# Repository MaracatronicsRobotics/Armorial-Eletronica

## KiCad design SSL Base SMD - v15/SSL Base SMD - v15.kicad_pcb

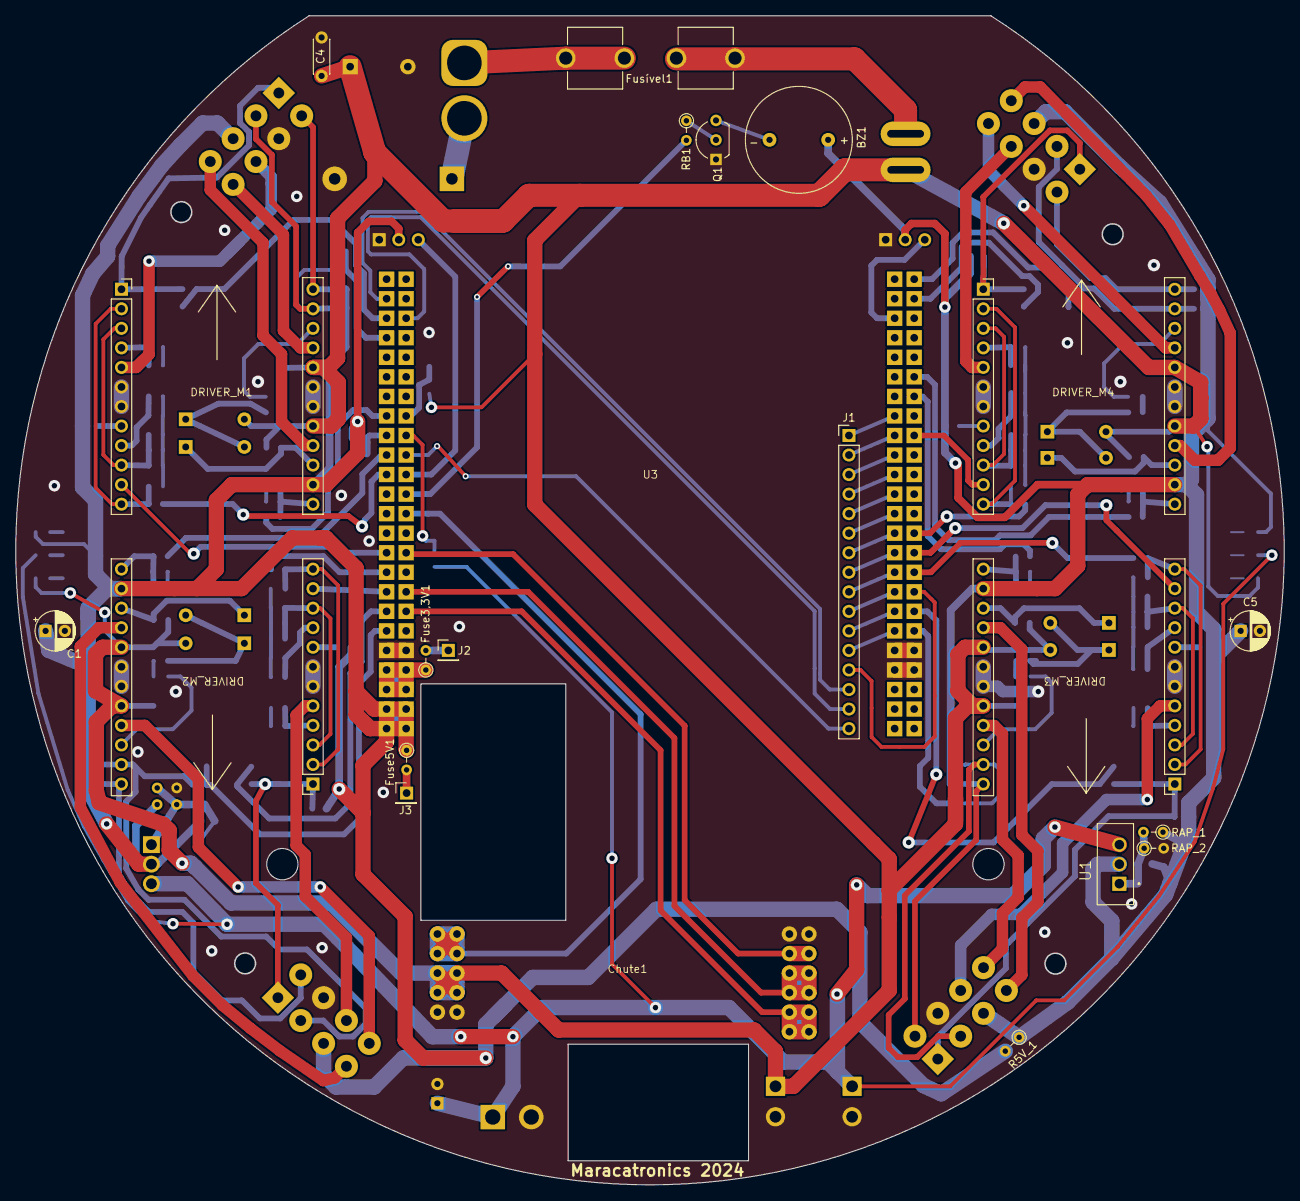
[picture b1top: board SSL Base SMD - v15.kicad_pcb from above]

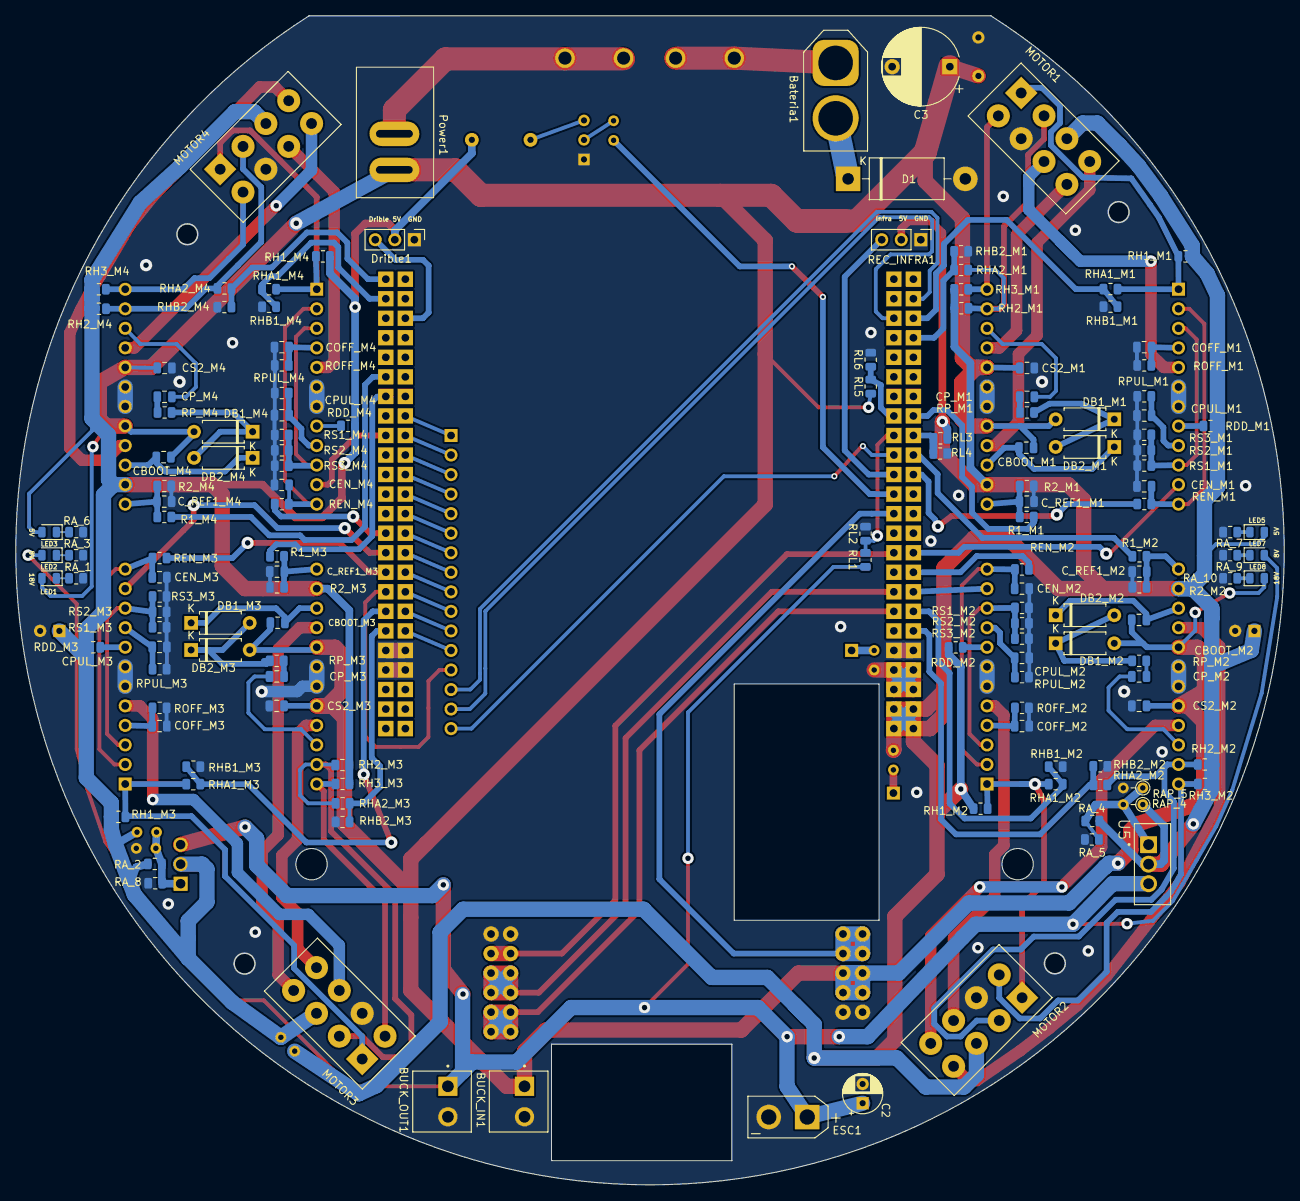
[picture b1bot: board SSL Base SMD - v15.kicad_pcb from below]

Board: 2 copper layers, 164.9 x 152.0 mm, 165 parts (143 on the bottom side), 131 nets.

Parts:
BUCK_IN1: Entrada_Buck_5V; TE_640388-2
BUCK_OUT1: Saida_Buck_5V; TE_640388-2
BZ1: Buzzer; XDCR_CPI-137-12T
Bateria1: Bateria; AMASS_XT60-M_1x02_P7.20mm_Vertical
C1, C2, C5: 100u; CP_Radial_D5.0mm_P2.50mm
C3: 220u; CP_Radial_D10.0mm_P7.50mm
C4: 100n; C_Disc_D4.3mm_W1.9mm_P5.00mm
CBOOT_M1, CBOOT_M2, CBOOT_M3, CBOOT_M4: 220n; C_0805_2012Metric
CEN_M1, CEN_M2, CEN_M3, CEN_M4: 10n; C_0805_2012Metric
COFF_M1, COFF_M2, COFF_M3, COFF_M4: 1n; C_0805_2012Metric
CPUL_M1, CPUL_M2, CPUL_M3, CPUL_M4: 10n; C_0805_2012Metric
CP_M1, CP_M2, CP_M3, CP_M4: 100n; C_0805_2012Metric
CS2_M1, CS2_M2, CS2_M3, CS2_M4: 100n; C_0805_2012Metric
C_REF1_M1, C_REF1_M2, C_REF1_M3, C_REF1_M4: 33n; C_0805_2012Metric
Chute1: Chute1; Conn_2x11x2_Maraca_Chute_Placa
D1: 1N5408; D_DO-201AD_P15.24mm_Horizontal
DB1_M1, DB1_M2, DB1_M3, DB1_M4, DB2_M1, DB2_M2, DB2_M3, DB2_M4: 1N4148; D_A-405_P7.62mm_Horizontal
DRIVER_M1, DRIVER_M2, DRIVER_M3, DRIVER_M4: L6235D; Adaptador L6235
Drible1: JST 3 PIN - ESC; PinHeader_1x03_P2.54mm_Vertical
ESC1: XT30PB - ESC_DRIBLE_POWER; AMASS_XT30UPB-F_1x02_P5.0mm_Vertical
Fuse3,3V1, Fuse5V1: 0; R_Axial_DIN0204_L3.6mm_D1.6mm_P2.54mm_Vertical
Fusível1: Fusível; FUSE_BK-6003M
J1: Conn_01x16; PinHeader_1x16_P2.54mm_Vertical
J2, J3: Conn_01x01; PinHeader_1x01_P2.54mm_Vertical
LED1, LED2, LED3, LED5, LED7, LED8: NCD0805R1; LED_0805_2012Metric
MOTOR1: CONECTOR MOTOR 1; TE_1586037-8b
MOTOR2: CONECTOR MOTOR 2; TE_1586037-8b
MOTOR3: CONECTOR MOTOR 3; TE_1586037-8b
MOTOR4: CONECTOR MOTOR 4; TE_1586037-8b
Power1: INTERRUPTOR; E-SWITCH_Maraca
Q1: 2N3904; TO-92L_Inline_Wide
R1_M1, R1_M2, R1_M3, R1_M4: 22k; R_0805_2012Metric
R2_M1, R2_M2, R2_M3, R2_M4: 3.3k; R_0805_2012Metric
R5V_1: 0; R_Axial_DIN0204_L3.6mm_D1.6mm_P2.54mm_Vertical
RAP_1, RAP_4: 1k; R_Axial_DIN0204_L3.6mm_D1.6mm_P2.54mm_Vertical
RAP_2, RAP_5: 3.3k; R_Axial_DIN0204_L3.6mm_D1.6mm_P2.54mm_Vertical
RA_1, RA_10: 2.2k; R_0805_2012Metric
RA_2, RA_3, RA_4, RA_9: 1k; R_0805_2012Metric
RA_5, RA_8: 3.3k; R_0805_2012Metric
RA_6, RA_7: 470; R_0805_2012Metric
RB1: 220; R_Axial_DIN0204_L3.6mm_D1.6mm_P2.54mm_Vertical
RDD_M1, RDD_M2, RDD_M3, RDD_M4: 1k; R_0805_2012Metric
REC_INFRA1: JST 3 PIN - INFRA; PinHeader_1x03_P2.54mm_Vertical
REN_M1, REN_M2, REN_M3, REN_M4: 100k; R_0805_2012Metric
RH1_M1, RH1_M2, RH1_M3, RH1_M4, RH2_M1, RH2_M2, RH2_M3, RH2_M4, RH3_M1, RH3_M2, RH3_M3, RH3_M4: 10k; R_0805_2012Metric
RHA1_M1, RHA1_M2, RHA1_M3, RHA1_M4, RHA2_M1, RHA2_M2, RHA2_M3, RHA2_M4: 1k; R_0805_2012Metric
RHB1_M1, RHB1_M2, RHB1_M3, RHB1_M4, RHB2_M1, RHB2_M2, RHB2_M3, RHB2_M4: 2.2k; R_0805_2012Metric
RL1, RL3, RL5: 10M; R_0805_2012Metric
RL2, RL4, RL6: 1M; R_0805_2012Metric
ROFF_M1, ROFF_M2, ROFF_M3, ROFF_M4: 33k; R_0805_2012Metric
RPUL_M1, RPUL_M2, RPUL_M3, RPUL_M4: 47k; R_0805_2012Metric
RP_M1, RP_M2, RP_M3, RP_M4: 100; R_0805_2012Metric
RS1_M1, RS1_M2, RS1_M3, RS1_M4, RS2_M1, RS2_M2, RS2_M3, RS2_M4, RS3_M1, RS3_M2, RS3_M3, RS3_M4: 1; R_0805_2012Metric
U1, U5: LM338T; TO254P1054X470X1955-3
U3: STM32F401VETx; STM32MARACA_3D

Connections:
3,3V: Fuse3,3V1.1, U3.69 (+3.3V_(4)), U3.70 (+3.3V_(3)), U3.93 (+3.3V_(2)), U3.94 (+3.3V_(1))
5BV: BZ1.1 (-), C5.1, DRIVER_M3.14 (BRAKE), DRIVER_M4.14 (BRAKE), Drible1.2, LED3.2 (A), MOTOR3.3, MOTOR4.3, R5V_1.1, RAP_1.1, RA_2.1, RDD_M3.1, RDD_M4.1, RH1_M3.2, RH1_M4.2, RH2_M3.2, RH2_M4.2, RH3_M3.2, RH3_M4.2, U1.2 (VOUT)
5V: C1.1, DRIVER_M1.14 (BRAKE), DRIVER_M2.14 (BRAKE), Fuse5V1.1, LED5.2 (A), MOTOR1.3, MOTOR2.3, R5V_1.2, RAP_4.1, RA_4.1, RDD_M1.1, RDD_M2.1, REC_INFRA1.2, RH1_M1.2, RH1_M2.2, RH2_M1.2, RH2_M2.2, RH3_M1.2, RH3_M2.2, RL3.1, U3.71 (+5V_(4)), U3.72 (+5V_(3)), U3.95 (+5V_(2)), U3.96 (+5V_(1)), U5.2 (VOUT)
8V: BUCK_OUT1.1, C2.1, ESC1.1, LED2.2 (A), LED7.2 (A), RL1.1, U1.3 (VIN), U5.3 (VIN)
18V: BUCK_IN1.1, C3.1, C4.1, CBOOT_M1.1, CBOOT_M2.1, CBOOT_M3.1, CBOOT_M4.1, CS2_M1.1, CS2_M2.1, CS2_M3.1, CS2_M4.1, Chute1.3, Chute1.4, DB1_M1.2 (A), DB1_M2.2 (A), DB1_M3.2 (A), DB1_M4.2 (A), DRIVER_M1.17 (VSB), DRIVER_M1.20 (VSA), DRIVER_M2.17 (VSB), DRIVER_M2.20 (VSA), DRIVER_M3.17 (VSB), DRIVER_M3.20 (VSA), DRIVER_M4.17 (VSB), DRIVER_M4.20 (VSA), LED1.2 (A), LED8.2 (A), Power1.1, RL5.1
ADC_Chute: Chute1.7, U3.63 (PC_3)
AnalogIN: J1.16, U3.58 (PA_7)
BAT_NEG: Bateria1.2, D1.1 (K)
BAT_POS: Bateria1.1, Fusível1.2
Buzzer: RB1.2, U3.60 (PA_3)
DIAG/EN_M1: CEN_M1.1, DRIVER_M1.2 (DIAG), DRIVER_M1.12 (EN), REN_M1.2
DIAG/EN_M2: CEN_M2.1, DRIVER_M2.2 (DIAG), DRIVER_M2.12 (EN), REN_M2.2
DIAG/EN_M3: CEN_M3.1, DRIVER_M3.2 (DIAG), DRIVER_M3.12 (EN), REN_M3.2
DIAG/EN_M4: CEN_M4.1, DRIVER_M4.2 (DIAG), DRIVER_M4.12 (EN), REN_M4.2
DISPARO CHIP KICK: Chute1.10, Chute1.11, U3.66 (PE_5)
DISPARO NORMAL: Chute1.8, Chute1.9, U3.65 (PC_13)
DRIBLE: Drible1.3, U3.27 (PD_12)
EN_M1: REN_M1.1, U3.83 (PA_4)
EN_M2: REN_M2.1, U3.88 (PC_0)
EN_M3: REN_M3.1, U3.16 (PB_3)
EN_M4: REN_M4.1, U3.14 (PD_4)
FWD/REV_M1: DRIVER_M1.11 (FWD/REV), U3.87 (PC_2)
FWD/REV_M2: DRIVER_M2.11 (FWD/REV), U3.89 (PE_6)
FWD/REV_M3: DRIVER_M3.11 (FWD/REV), U3.15 (PD_6)
FWD/REV_M4: DRIVER_M4.11 (FWD/REV), U3.9 (PA_11)
GND: BUCK_IN1.2, BUCK_OUT1.2, C1.2, C2.2, C3.2, C4.2, C5.2, CEN_M1.2, CEN_M2.2, CEN_M3.2, CEN_M4.2, COFF_M1.2, COFF_M2.2, COFF_M3.2, COFF_M4.2, CPUL_M1.2, CPUL_M2.2, CPUL_M3.2, CPUL_M4.2, CS2_M1.2, CS2_M2.2, CS2_M3.2, CS2_M4.2, C_REF1_M1.2, C_REF1_M2.2, C_REF1_M3.2, C_REF1_M4.2, Chute1.5, Chute1.6, D1.2 (A), DRIVER_M1.6 (GND), DRIVER_M1.7 (GND), DRIVER_M1.18 (GND), DRIVER_M1.19 (GND), DRIVER_M2.6 (GND), DRIVER_M2.7 (GND), DRIVER_M2.18 (GND), DRIVER_M2.19 (GND), DRIVER_M3.6 (GND), DRIVER_M3.7 (GND), DRIVER_M3.18 (GND), DRIVER_M3.19 (GND), DRIVER_M4.6 (GND), DRIVER_M4.7 (GND), DRIVER_M4.18 (GND), DRIVER_M4.19 (GND), Drible1.1, ESC1.2, MOTOR1.6, MOTOR2.6, MOTOR3.6, MOTOR4.6, Q1.1 (E), R2_M1.2, R2_M2.2, R2_M3.2, R2_M4.2, RAP_2.2, RAP_5.2, RA_1.2, RA_3.2, RA_5.2, RA_6.2, RA_7.2, RA_8.2, RA_9.2, RA_10.2, REC_INFRA1.1, RHB1_M1.2, RHB1_M2.2, RHB1_M3.2, RHB1_M4.2, RHB2_M1.2, RHB2_M2.2, RHB2_M3.2, RHB2_M4.2, RL2.2, RL4.2, RL6.2, ROFF_M1.2, ROFF_M2.2, ROFF_M3.2, ROFF_M4.2, RPUL_M1.2, RPUL_M2.2, RPUL_M3.2, RPUL_M4.2, RS1_M1.1, RS1_M2.1, RS1_M3.1, RS1_M4.1, RS2_M1.1, RS2_M2.1, RS2_M3.1, RS2_M4.1, RS3_M1.1, RS3_M2.1, RS3_M3.1, RS3_M4.1, U3.20 (GND_(6)), U3.21 (GND_(5)), U3.44 (GND_(4)), U3.45 (GND_(3)), U3.68 (GND_(2)), U3.92 (GND_(1))
H1_M1: RHA1_M1.2, RHB1_M1.1, U3.75 (PE_15)
H1_M2: RHA1_M2.2, RHB1_M2.1, U3.90 (PE_4)
H1_M3: RHA1_M3.2, RHB1_M3.1, U3.18 (PB_8)
H1_M4: RHA1_M4.2, RHB1_M4.1, U3.2 (PD_9)
H2_M1: RHA2_M1.2, RHB2_M1.1, U3.76 (PE_13)
H2_M2: RHA2_M2.2, RHB2_M2.1, U3.91 (PE_2)
H2_M3: RHA2_M3.2, RHB2_M3.1, U3.19 (PE_0)
H2_M4: RHA2_M4.2, RHB2_M4.1, U3.1 (PB_15)
HALL1_M1: DRIVER_M1.1 (H1), MOTOR1.1, RH1_M1.1, RHA1_M1.1
HALL1_M2: DRIVER_M2.1 (H1), MOTOR2.1, RH1_M2.1, RHA1_M2.1
HALL1_M3: DRIVER_M3.1 (H1), MOTOR3.1, RH1_M3.1, RHA1_M3.1
HALL1_M4: DRIVER_M4.1 (H1), MOTOR4.1, RH1_M4.1, RHA1_M4.1
HALL2_M1: DRIVER_M1.23 (H2), MOTOR1.2, RH2_M1.1, RHA2_M1.1
HALL2_M2: DRIVER_M2.23 (H2), MOTOR2.2, RH2_M2.1, RHA2_M2.1
HALL2_M3: DRIVER_M3.23 (H2), MOTOR3.2, RH2_M3.1, RHA2_M3.1
HALL2_M4: DRIVER_M4.23 (H2), MOTOR4.2, RH2_M4.1, RHA2_M4.1
HALL3_M1: DRIVER_M1.24 (H3), MOTOR1.5, RH3_M1.1
HALL3_M2: DRIVER_M2.24 (H3), MOTOR2.5, RH3_M2.1
HALL3_M3: DRIVER_M3.24 (H3), MOTOR3.5, RH3_M3.1
HALL3_M4: DRIVER_M4.24 (H3), MOTOR4.5, RH3_M4.1
INFRA: REC_INFRA1.3, U3.59 (PA_5)
LEITURA_5V: RL3.2, RL4.1, U3.81 (PC_4)
LEITURA_8V: RL1.2, RL2.1, U3.57 (PC_5)
LEITURA_BATERIA: RL5.2, RL6.1, U3.56 (PB_1)
MOTOR1_1: DRIVER_M1.5 (OUT1), MOTOR1.7
MOTOR1_2: DRIVER_M1.21 (OUT2), MOTOR1.8
MOTOR1_3: DRIVER_M1.16 (OUT3), MOTOR1.4
MOTOR2_1: DRIVER_M2.5 (OUT1), MOTOR2.7
MOTOR2_2: DRIVER_M2.21 (OUT2), MOTOR2.8
MOTOR2_3: DRIVER_M2.16 (OUT3), MOTOR2.4
MOTOR3_1: DRIVER_M3.5 (OUT1), MOTOR3.7
MOTOR3_2: DRIVER_M3.21 (OUT2), MOTOR3.8
MOTOR3_3: DRIVER_M3.16 (OUT3), MOTOR3.4
MOTOR4_1: DRIVER_M4.5 (OUT1), MOTOR4.7
MOTOR4_2: DRIVER_M4.21 (OUT2), MOTOR4.8
MOTOR4_3: DRIVER_M4.16 (OUT3), MOTOR4.4
unnamed: BZ1.2 (+), Q1.3 (C)
unnamed: CP_M1.2, RP_M1.1
unnamed: CP_M2.2, RP_M2.1
unnamed: CP_M3.2, RP_M3.1
unnamed: CP_M4.2, RP_M4.1
unnamed: DB1_M1.1 (K), DB2_M1.2 (A), RP_M1.2
unnamed: DB1_M2.1 (K), DB2_M2.2 (A), RP_M2.2
unnamed: DB1_M3.1 (K), DB2_M3.2 (A), RP_M3.2
unnamed: DB1_M4.1 (K), DB2_M4.2 (A), RP_M4.2
unnamed: Fusível1.1, Power1.2
unnamed: LED1.1 (K), RA_1.1
unnamed: LED2.1 (K), RA_3.1
unnamed: LED3.1 (K), RA_6.1
unnamed: LED5.1 (K), RA_7.1
unnamed: LED7.1 (K), RA_9.1
unnamed: LED8.1 (K), RA_10.1
unnamed: Q1.2 (B), RB1.1
unnamed: RAP_1.2, RAP_2.1, RA_2.2, RA_8.1, U1.1 (ADJ)
unnamed: RAP_4.2, RAP_5.1, RA_4.2, RA_5.1, U5.1 (ADJ)
Out 3,3V: Fuse3,3V1.2, J2.1
Out 5V: Fuse5V1.2, J3.1
PA10: J1.1, U3.32 (PA_10)
PA12: J1.2, U3.33 (PA_12)
PB5: J1.9, U3.40 (PB_5)
PB6: J1.13, U3.17 (PB_6)
PB7: J1.10, U3.41 (PB_7)
PB9: J1.11, U3.42 (PB_9)
PB10: J1.15, U3.51 (PB_10)
PB11: J1.14, U3.74 (PB_11)
PC10: J1.3, U3.34 (PC_10)
PC12: J1.4, U3.35 (PC_12)
PD1: J1.5, U3.36 (PD_1)
PD3: J1.6, U3.37 (PD_3)
PD5: J1.7, U3.38 (PD_5)
PD7: J1.8, U3.39 (PD_7)
PE1: J1.12, U3.43 (PE_1)
PWM_Carregamento: Chute1.1, Chute1.2, U3.61 (PA_1)
PWM_RODA_1: R1_M1.2, U3.80 (PB_0)
PWM_RODA_2: R1_M2.2, U3.82 (PA_6)
PWM_RODA_3: R1_M3.2, U3.7 (PC_9)
PWM_RODA_4: R1_M4.2, U3.6 (PC_7)
RCOFF_M1: COFF_M1.1, DRIVER_M1.4 (RCOFF), ROFF_M1.1
RCOFF_M2: COFF_M2.1, DRIVER_M2.4 (RCOFF), ROFF_M2.1
RCOFF_M3: COFF_M3.1, DRIVER_M3.4 (RCOFF), ROFF_M3.1
RCOFF_M4: COFF_M4.1, DRIVER_M4.4 (RCOFF), ROFF_M4.1
RCPULSE_M1: CPUL_M1.1, DRIVER_M1.9 (RCPULSE), RPUL_M1.1
RCPULSE_M2: CPUL_M2.1, DRIVER_M2.9 (RCPULSE), RPUL_M2.1
RCPULSE_M3: CPUL_M3.1, DRIVER_M3.9 (RCPULSE), RPUL_M3.1
RCPULSE_M4: CPUL_M4.1, DRIVER_M4.9 (RCPULSE), RPUL_M4.1
SENSE_M1: DRIVER_M1.3 (SENSEA), DRIVER_M1.10 (SENSEB), RS1_M1.2, RS2_M1.2, RS3_M1.2
SENSE_M2: DRIVER_M2.3 (SENSEA), DRIVER_M2.10 (SENSEB), RS1_M2.2, RS2_M2.2, RS3_M2.2
SENSE_M3: DRIVER_M3.3 (SENSEA), DRIVER_M3.10 (SENSEB), RS1_M3.2, RS2_M3.2, RS3_M3.2
SENSE_M4: DRIVER_M4.3 (SENSEA), DRIVER_M4.10 (SENSEB), RS1_M4.2, RS2_M4.2, RS3_M4.2
TACHO_M1: DRIVER_M1.8 (TACHO), RDD_M1.2
TACHO_M2: DRIVER_M2.8 (TACHO), RDD_M2.2
TACHO_M3: DRIVER_M3.8 (TACHO), RDD_M3.2
TACHO_M4: DRIVER_M4.8 (TACHO), RDD_M4.2
VBOOT_M1: CBOOT_M1.2, DB2_M1.1 (K), DRIVER_M1.15 (VBOOT)
VBOOT_M2: CBOOT_M2.2, DB2_M2.1 (K), DRIVER_M2.15 (VBOOT)
VBOOT_M3: CBOOT_M3.2, DB2_M3.1 (K), DRIVER_M3.15 (VBOOT)
VBOOT_M4: CBOOT_M4.2, DB2_M4.1 (K), DRIVER_M4.15 (VBOOT)
VCP_M1: CP_M1.1, DRIVER_M1.22 (VCP)
VCP_M2: CP_M2.1, DRIVER_M2.22 (VCP)
VCP_M3: CP_M3.1, DRIVER_M3.22 (VCP)
VCP_M4: CP_M4.1, DRIVER_M4.22 (VCP)
VREF_M1: C_REF1_M1.1, DRIVER_M1.13 (VREF), R1_M1.1, R2_M1.1
VREF_M2: C_REF1_M2.1, DRIVER_M2.13 (VREF), R1_M2.1, R2_M2.1
VREF_M3: C_REF1_M3.1, DRIVER_M3.13 (VREF), R1_M3.1, R2_M3.1
VREF_M4: C_REF1_M4.1, DRIVER_M4.13 (VREF), R1_M4.1, R2_M4.1

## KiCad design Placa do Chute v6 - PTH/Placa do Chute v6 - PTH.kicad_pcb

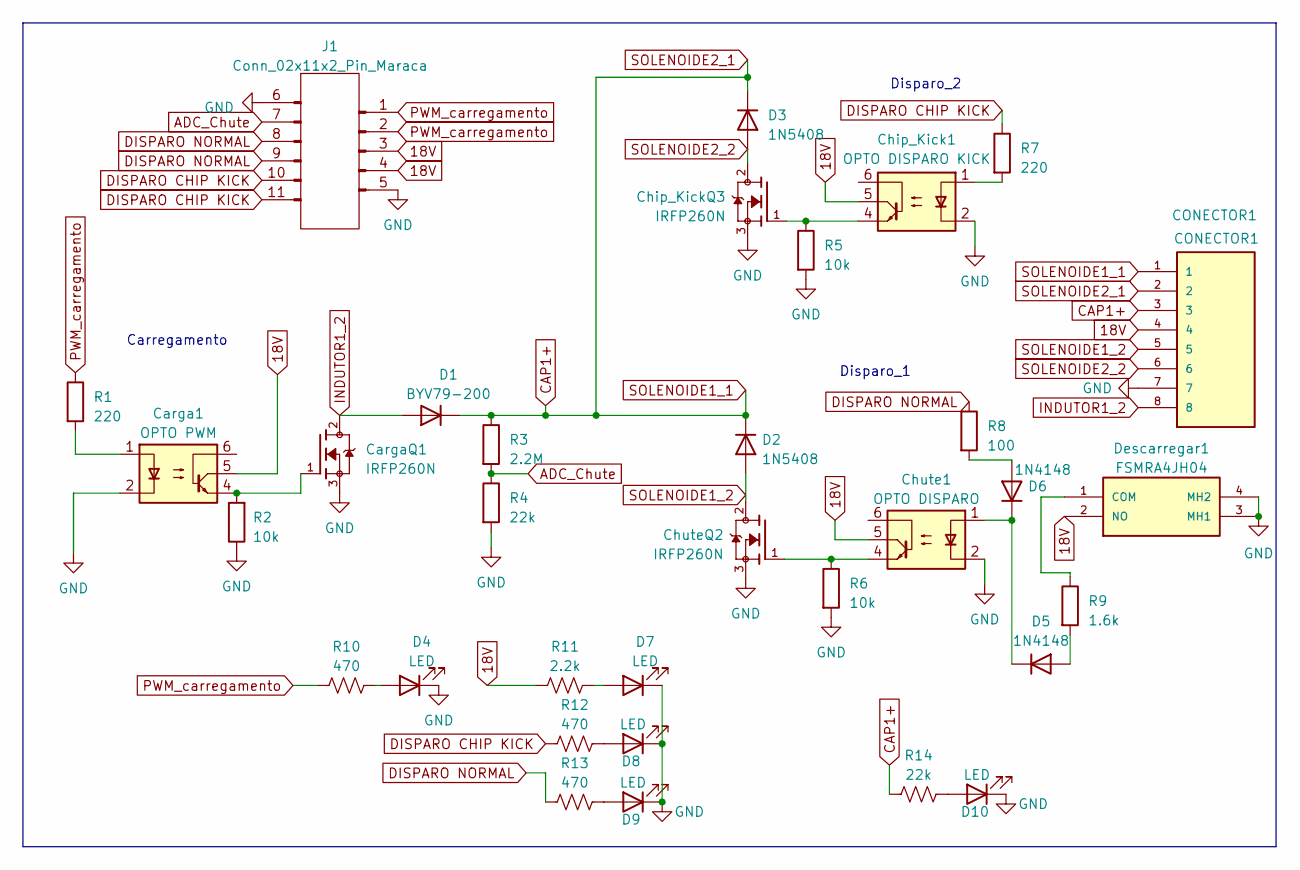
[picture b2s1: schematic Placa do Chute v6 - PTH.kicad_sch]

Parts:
CONECTOR1: CONECTOR1; TE_1586037-8b
Carga1: OPTO PWM; DIP-6_W7.62mm
CargaQ1: IRFP260N; TO545P1560X500X2460-3 90d; PARTREV 08/18/10
Chip_Kick1: OPTO DISPARO KICK; DIP-6_W7.62mm
Chip_KickQ3: IRFP260N; TO545P1560X500X2460-3 90d; PARTREV 08/18/10
Chute1: OPTO DISPARO; DIP-6_W7.62mm
ChuteQ2: IRFP260N; TO545P1560X500X2460-3 90d; PARTREV 08/18/10
D1: BYV79-200; TO-220-2_Horizontal_TabDown
D2, D3: 1N5408; D_DO-201AD_P15.24mm_Horizontal
D4, D7, D8, D9, D10: LED; LED_D3.0mm_Horizontal_O1.27mm_Z2.0mm
D5, D6: 1N4148; D_DO-35_SOD27_P7.62mm_Horizontal
Descarregar1: FSMRA4JH04; MOUSER_PART_NUMBER 506-FSMRA4JH04
J1: Conn_02x11x2_Pin_Maraca; Conn_2x11x2_Maraca_Chute
R1, R7: 220; R_Axial_DIN0207_L6.3mm_D2.5mm_P10.16mm_Horizontal
R2, R5, R6: 10k; R_Axial_DIN0207_L6.3mm_D2.5mm_P10.16mm_Horizontal
R3: 2.2M; R_Axial_DIN0207_L6.3mm_D2.5mm_P10.16mm_Horizontal
R4, R14: 22k; R_Axial_DIN0207_L6.3mm_D2.5mm_P10.16mm_Horizontal
R8: 100; R_Axial_DIN0207_L6.3mm_D2.5mm_P10.16mm_Horizontal
R9: 1.6k; R_Axial_DIN0207_L6.3mm_D2.5mm_P10.16mm_Horizontal
R10, R12, R13: 470; R_Axial_DIN0207_L6.3mm_D2.5mm_P10.16mm_Horizontal
R11: 2.2k; R_Axial_DIN0207_L6.3mm_D2.5mm_P10.16mm_Horizontal

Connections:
18V: CONECTOR1.4, Carga1.5, Chip_Kick1.5, Chute1.5, Descarregar1.2 (NO), J1.3, J1.4, R11.1
ADC_Chute: J1.7, R3.2, R4.1
CAP1+: CONECTOR1.1, CONECTOR1.2, CONECTOR1.3, D1.1 (K), D2.1 (K), D3.1 (K), R3.1, R14.1
DISPARO CHIP KICK: J1.10, J1.11, R7.1, R12.1
DISPARO NORMAL: J1.8, J1.9, R8.1, R13.1
GND: CONECTOR1.7, Carga1.2, CargaQ1.3, Chip_Kick1.2, Chip_KickQ3.3, Chute1.2, ChuteQ2.3, D4.1 (K), D7.1 (K), D8.1 (K), D9.1 (K), D10.1 (K), Descarregar1.3 (MH1), Descarregar1.4 (MH2), J1.5, J1.6, R2.1, R4.2, R5.2, R6.2
INDUTOR1_2: CONECTOR1.8, CargaQ1.2, D1.2 (A)
unnamed: Carga1.1, R1.2
unnamed: Carga1.4, CargaQ1.1, R2.2
unnamed: Chip_Kick1.1, R7.2
unnamed: Chip_Kick1.4, Chip_KickQ3.1, R5.1
unnamed: Chute1.4, ChuteQ2.1, R6.1
unnamed: D4.2 (A), R10.2
unnamed: D5.2 (A), R9.2
unnamed: Chute1.1, D5.1 (K), D6.1 (K)
unnamed: D6.2 (A), R8.2
unnamed: D7.2 (A), R11.2
unnamed: D8.2 (A), R12.2
unnamed: D9.2 (A), R13.2
unnamed: D10.2 (A), R14.2
unnamed: Descarregar1.1 (COM), R9.1
PWM_carregamento: J1.1, J1.2, R1.1, R10.1
SOLENOIDE1_2: CONECTOR1.5, ChuteQ2.2, D2.2 (A)
SOLENOIDE2_2: CONECTOR1.6, Chip_KickQ3.2, D3.2 (A)

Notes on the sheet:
Disparo_2
Carregamento
Disparo_1

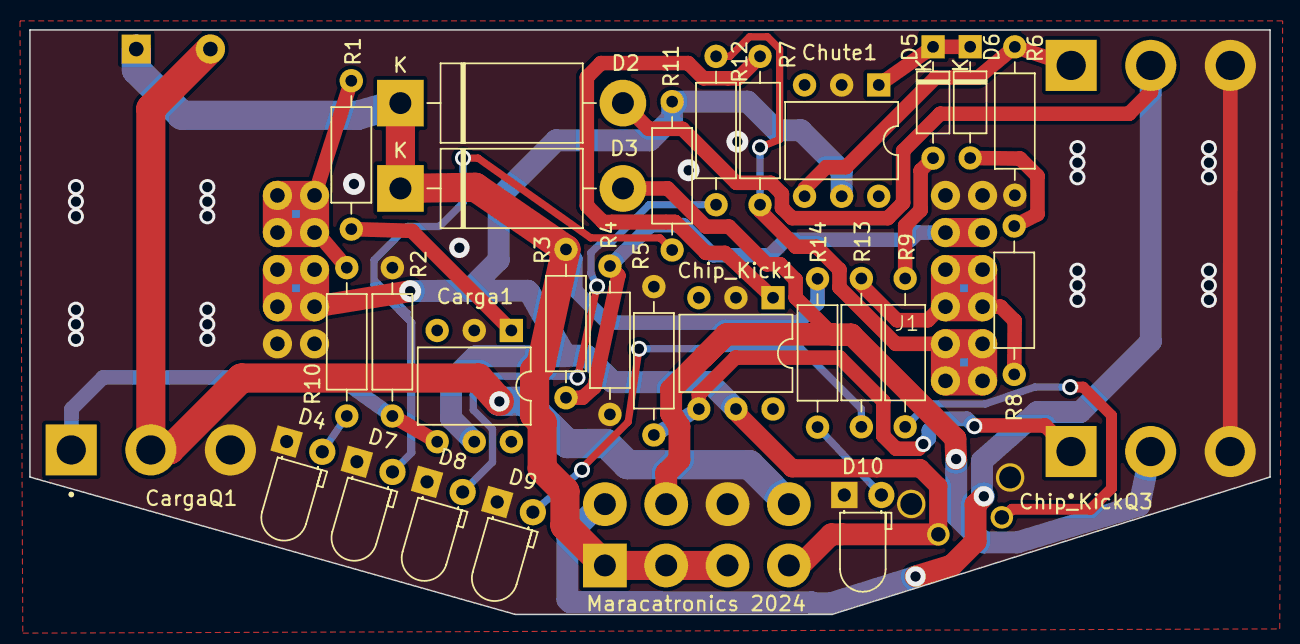
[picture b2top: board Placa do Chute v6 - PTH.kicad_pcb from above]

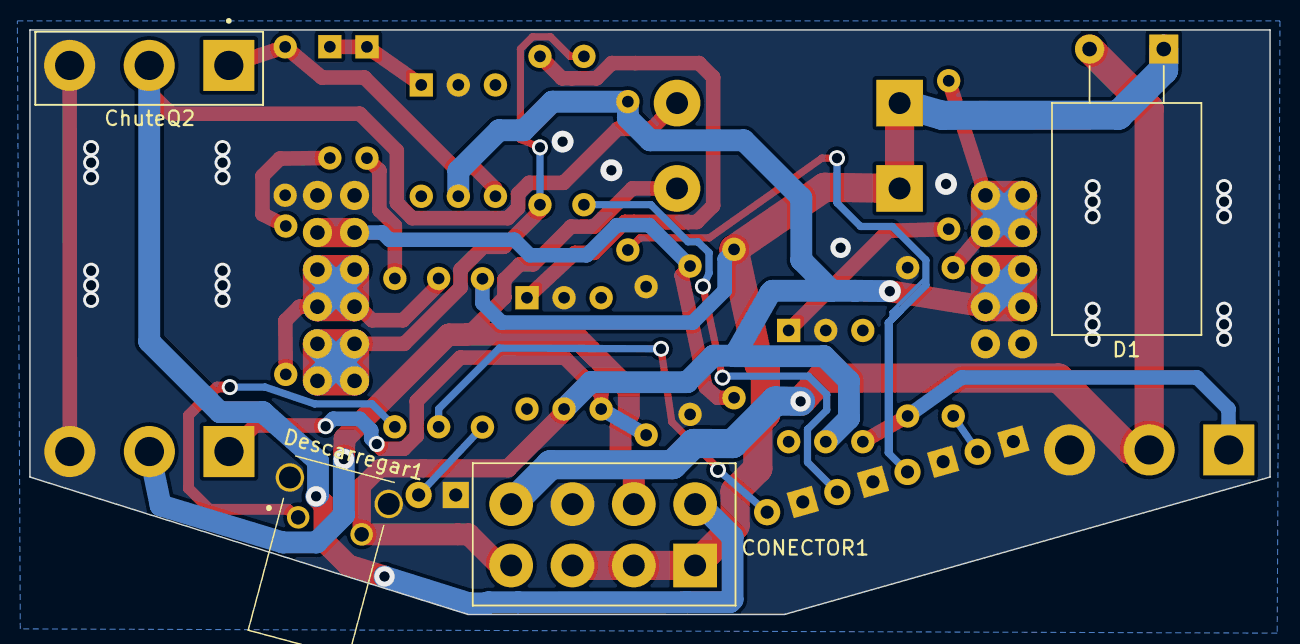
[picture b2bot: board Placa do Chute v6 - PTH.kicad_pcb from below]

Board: 2 copper layers, 84.9 x 40.0 mm, 33 parts (4 on the bottom side), 24 nets.

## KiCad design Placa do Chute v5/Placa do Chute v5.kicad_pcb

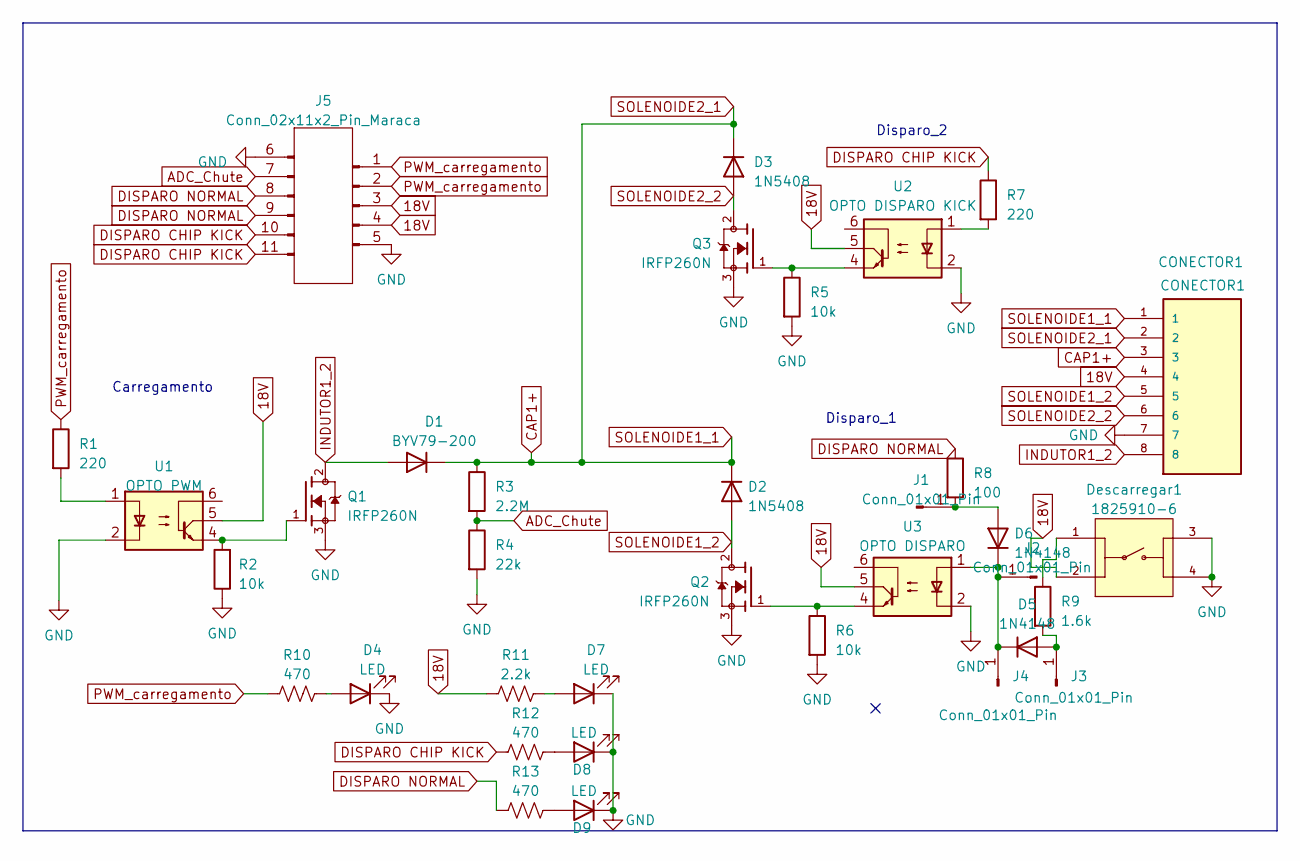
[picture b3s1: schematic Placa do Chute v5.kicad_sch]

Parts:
CONECTOR1: CONECTOR1; TE_1586037-8b
D1: BYV79-200; TO-220-2_Horizontal_TabDown
D2, D3: 1N5408; D_DO-201_P12.70mm_Horizontal
D4, D7, D8, D9: LED; LED_0805_2012Metric
D5, D6: 1N4148; D_0805_2012Metric
Descarregar1: 1825910-6; FSMRA4JH04
J1, J2, J3, J4: Conn_01x01_Pin; PinHeader_1x01_P2.54mm_Vertical
J5: Conn_02x11x2_Pin_Maraca; Conn_2x11x2_Maraca_Chute
Q1, Q2, Q3: IRFP260N; TO545P1560X500X2460-3 90d; PARTREV 08/18/10
R1, R7: 220; R_0805_2012Metric
R2, R5, R6: 10k; R_0805_2012Metric
R3: 2.2M; R_0805_2012Metric
R4: 22k; R_0805_2012Metric
R8: 100; R_0805_2012Metric
R9: 1.6k; R_0805_2012Metric
R10, R12, R13: 470; R_0805_2012Metric
R11: 2.2k; R_0805_2012Metric
U1: OPTO PWM; DIP-6_W7.62mm
U2: OPTO DISPARO KICK; DIP-6_W7.62mm
U3: OPTO DISPARO; DIP-6_W7.62mm

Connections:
18V: CONECTOR1.4, Descarregar1.2, J5.3, J5.4, R11.1, U1.5, U2.5, U3.5
ADC_Chute: J5.7, R3.2, R4.1
CAP1+: CONECTOR1.1, CONECTOR1.2, CONECTOR1.3, D1.1 (K), D2.1 (K), D3.1 (K), R3.1
DISPARO CHIP KICK: J5.10, J5.11, R7.1, R12.1
DISPARO NORMAL: J5.8, J5.9, R8.1, R13.1
GND: CONECTOR1.7, D4.1 (K), D7.1 (K), D8.1 (K), D9.1 (K), Descarregar1.3, Descarregar1.4, J5.5, J5.6, Q1.3, Q2.3, Q3.3, R2.1, R4.2, R5.2, R6.2, U1.2, U2.2, U3.2
INDUTOR1_2: CONECTOR1.8, D1.2 (A), Q1.2
unnamed: D4.2 (A), R10.2
unnamed: D5.2 (A), J3.1, R9.2
unnamed: D5.1 (K), D6.1 (K), J2.1, J4.1, U3.1
unnamed: D6.2 (A), J1.1, R8.2
unnamed: D7.2 (A), R11.2
unnamed: D8.2 (A), R12.2
unnamed: D9.2 (A), R13.2
unnamed: Descarregar1.1, R9.1
unnamed: Q1.1, R2.2, U1.4
unnamed: Q2.1, R6.1, U3.4
unnamed: Q3.1, R5.1, U2.4
unnamed: R1.2, U1.1
unnamed: R7.2, U2.1
PWM_carregamento: J5.1, J5.2, R1.1, R10.1
SOLENOIDE1_2: CONECTOR1.5, D2.2 (A), Q2.2
SOLENOIDE2_2: CONECTOR1.6, D3.2 (A), Q3.2

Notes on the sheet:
Disparo_2
Carregamento
Disparo_1

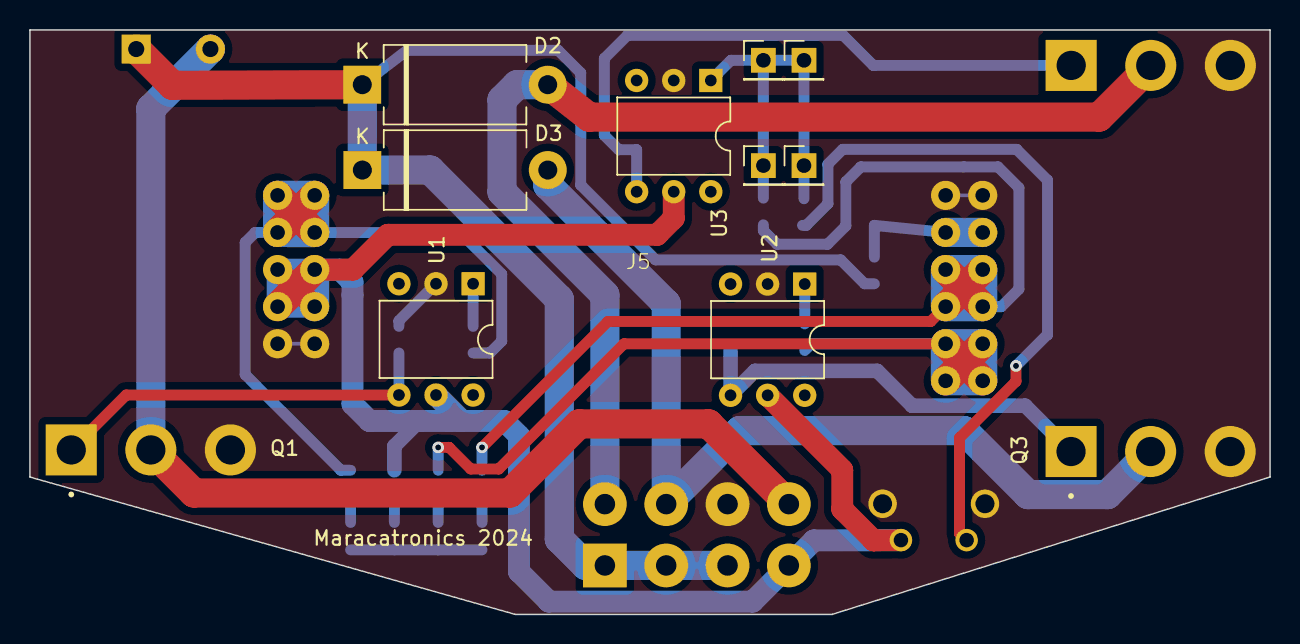
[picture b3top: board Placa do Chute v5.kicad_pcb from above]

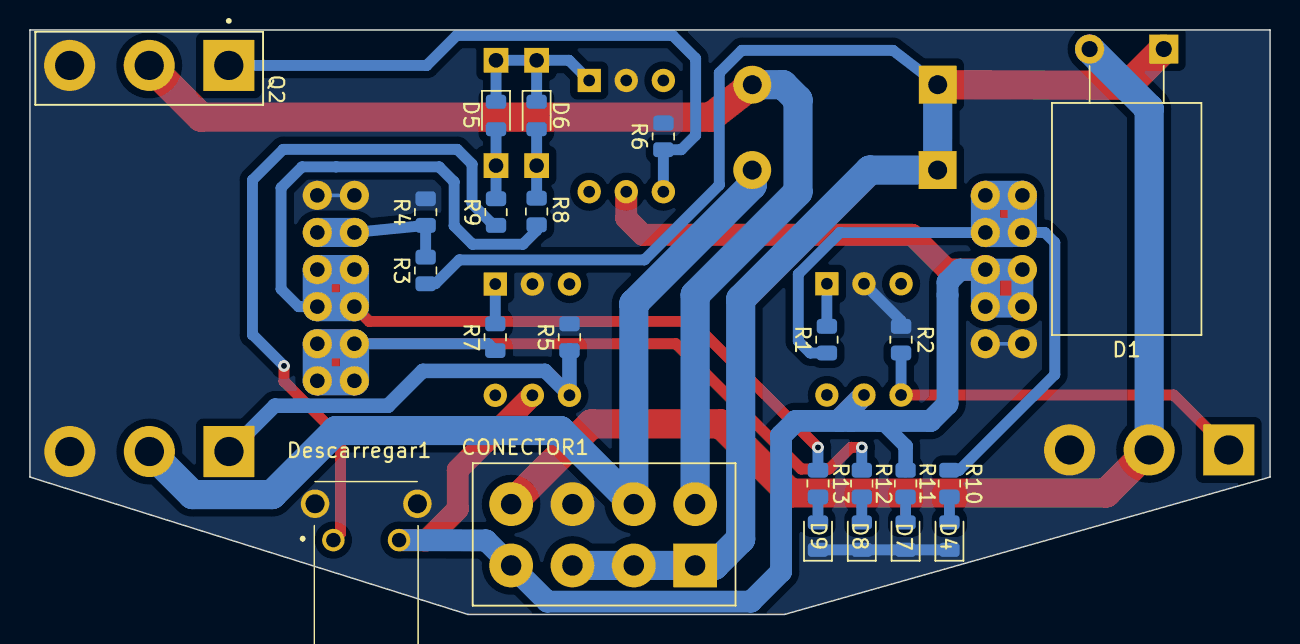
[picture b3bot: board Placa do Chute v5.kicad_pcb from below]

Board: 2 copper layers, 84.9 x 40.0 mm, 35 parts (23 on the bottom side), 23 nets.

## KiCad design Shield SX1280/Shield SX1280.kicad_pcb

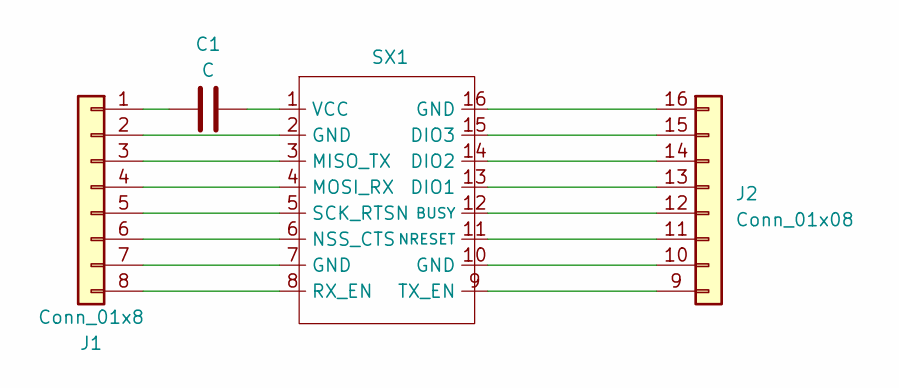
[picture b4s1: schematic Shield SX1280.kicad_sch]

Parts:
C1: C; CP_Radial_D5.0mm_P2.50mm
J1: Conn_01x8; PinHeader_1x08_P2.54mm_Vertical
J2: Conn_01x08; PinHeader_1x08_P2.54mm_Vertical
SX1: SX1280

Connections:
unnamed: C1.1, J1.1
unnamed: J1.2, SX1.2 (GND)
unnamed: J1.3, SX1.3 (MISO_TX)
unnamed: J1.4, SX1.4 (MOSI_RX)
unnamed: J1.5, SX1.5 (SCK_RTSN)
unnamed: J1.6, SX1.6 (NSS_CTS)
unnamed: J1.7, SX1.7 (GND)
unnamed: J1.8, SX1.8 (RX_EN)
unnamed: J2.16 (Pin_1), SX1.16 (GND)
unnamed: J2.15 (Pin_2), SX1.15 (DIO3)
unnamed: J2.14 (Pin_3), SX1.14 (DIO2)
unnamed: J2.13 (Pin_4), SX1.13 (DIO1)
unnamed: J2.12 (Pin_5), SX1.12 (BUSY)
unnamed: J2.11 (Pin_6), SX1.11 (NRESET)
unnamed: J2.10 (Pin_7), SX1.10 (GND)
unnamed: J2.9 (Pin_8), SX1.9 (TX_EN)
unnamed: C1.2, SX1.1 (VCC)

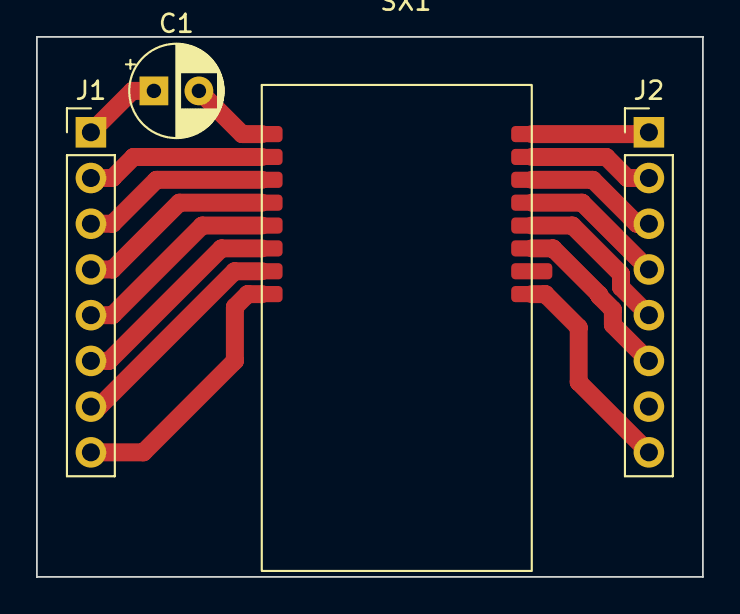
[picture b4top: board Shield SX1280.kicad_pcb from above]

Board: 2 copper layers, 37.0 x 30.0 mm, 4 parts (0 on the bottom side), 17 nets.

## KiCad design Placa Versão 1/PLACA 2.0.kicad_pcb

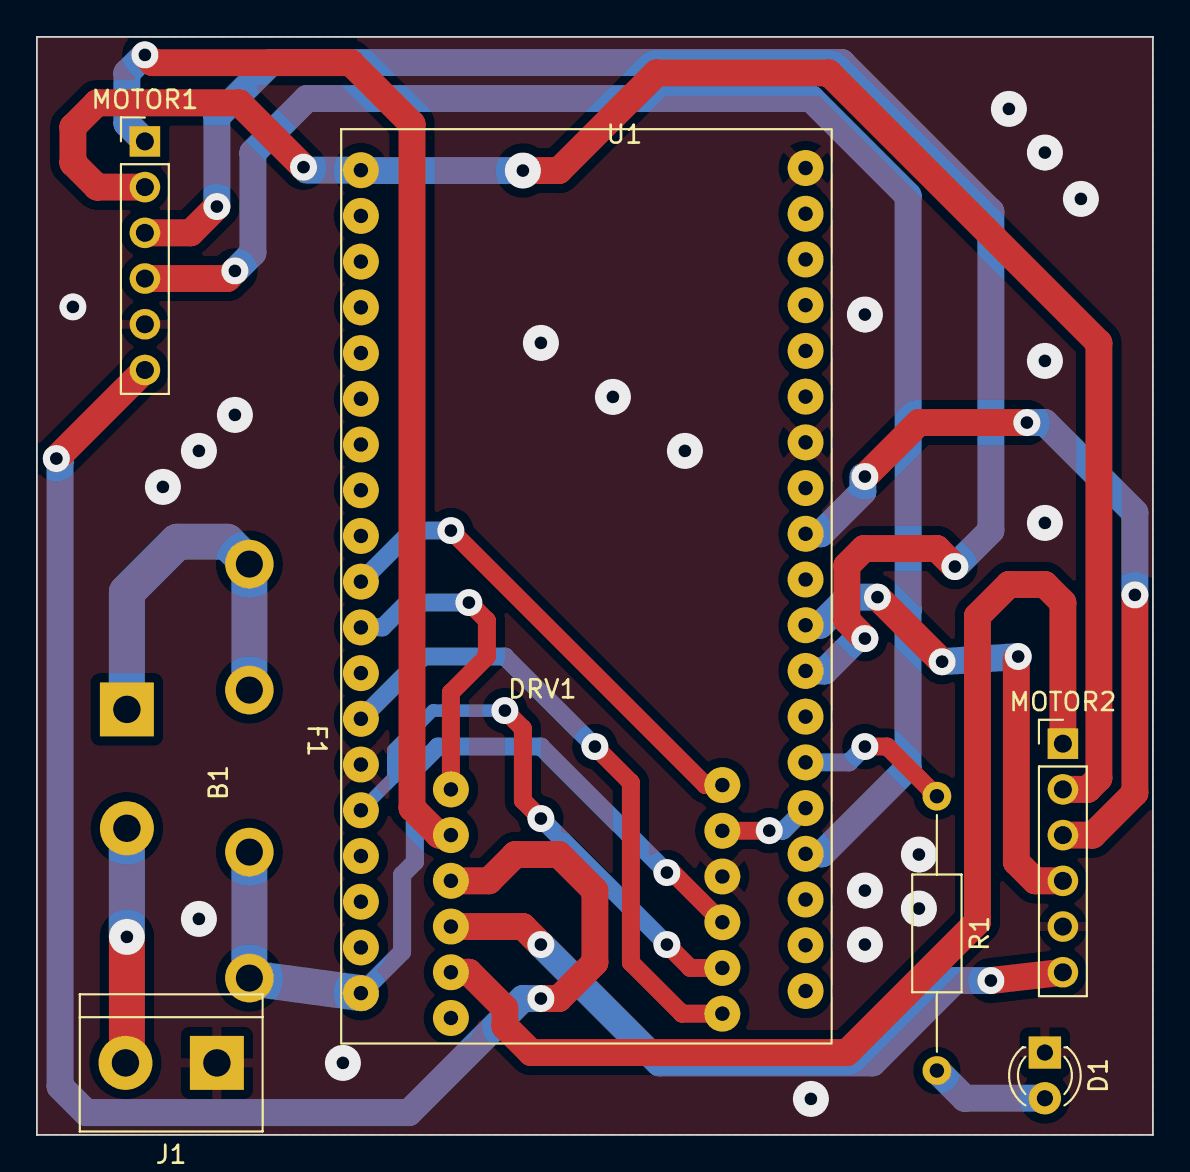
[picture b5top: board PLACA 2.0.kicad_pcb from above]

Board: 2 copper layers, 62.0 x 61.0 mm, 9 parts (0 on the bottom side), 17 nets.

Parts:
B1: SWITCH; TerminalBlock_bornier-2_P5.08mm
D1: LED; LED_D3.0mm
DRV1: DRV8833
F1: Fusivel; FUSIVEL
J1: Conn_01x02_Male; TerminalBlock_bornier-2_P5.08mm
MOTOR1, MOTOR2: Conn_01x06_Male; PinHeader_1x06_P2.54mm_Vertical
R1: R_US; R_Axial_DIN0207_L6.3mm_D2.5mm_P15.24mm_Horizontal
U1: ESP38PINOS; ESP 38 PINOS

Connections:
Earth: D1.1 (K), DRV1.A8 (GND), J1.e (Pin_1), MOTOR1.5, MOTOR2.5, U1.A13 (GND), U1.A19 (GND), U1.A25 (GND)
unnamed: D1.2 (A), R1.2
unnamed: DRV1.A0 (EEP), U1.A10 (G27)
unnamed: DRV1.A11 (IN1), U1.A12 (G12)
unnamed: DRV1.A10 (IN2), U1.A14 (G13)
unnamed: DRV1.A7 (IN3), U1.A33 (G2)
unnamed: DRV1.A6 (IN4), U1.A9 (G26)
unnamed: DRV1.A1 (OUT1), MOTOR1.1
unnamed: DRV1.A2 (OUT2), MOTOR1.6
unnamed: DRV1.A3 (OUT3), MOTOR2.6
unnamed: B1.1, DRV1.A9 (VCC), F1.A1, F1.A2, F1.A3, F1.A4, U1.A18 (5V)
unnamed: B1.2, J1.1 (Pin_2)
unnamed: DRV1.A4 (OUT4), MOTOR1.2, MOTOR2.1, MOTOR2.2, MOTOR2.4, U1.A0 (3V3), U1.A29 (G17)
unnamed: MOTOR1.3, U1.A30 (G16)
unnamed: MOTOR1.4, U1.A34 (G15)
unnamed: MOTOR2.3, U1.A27 (G18)
unnamed: R1.1, U1.A32 (G0)

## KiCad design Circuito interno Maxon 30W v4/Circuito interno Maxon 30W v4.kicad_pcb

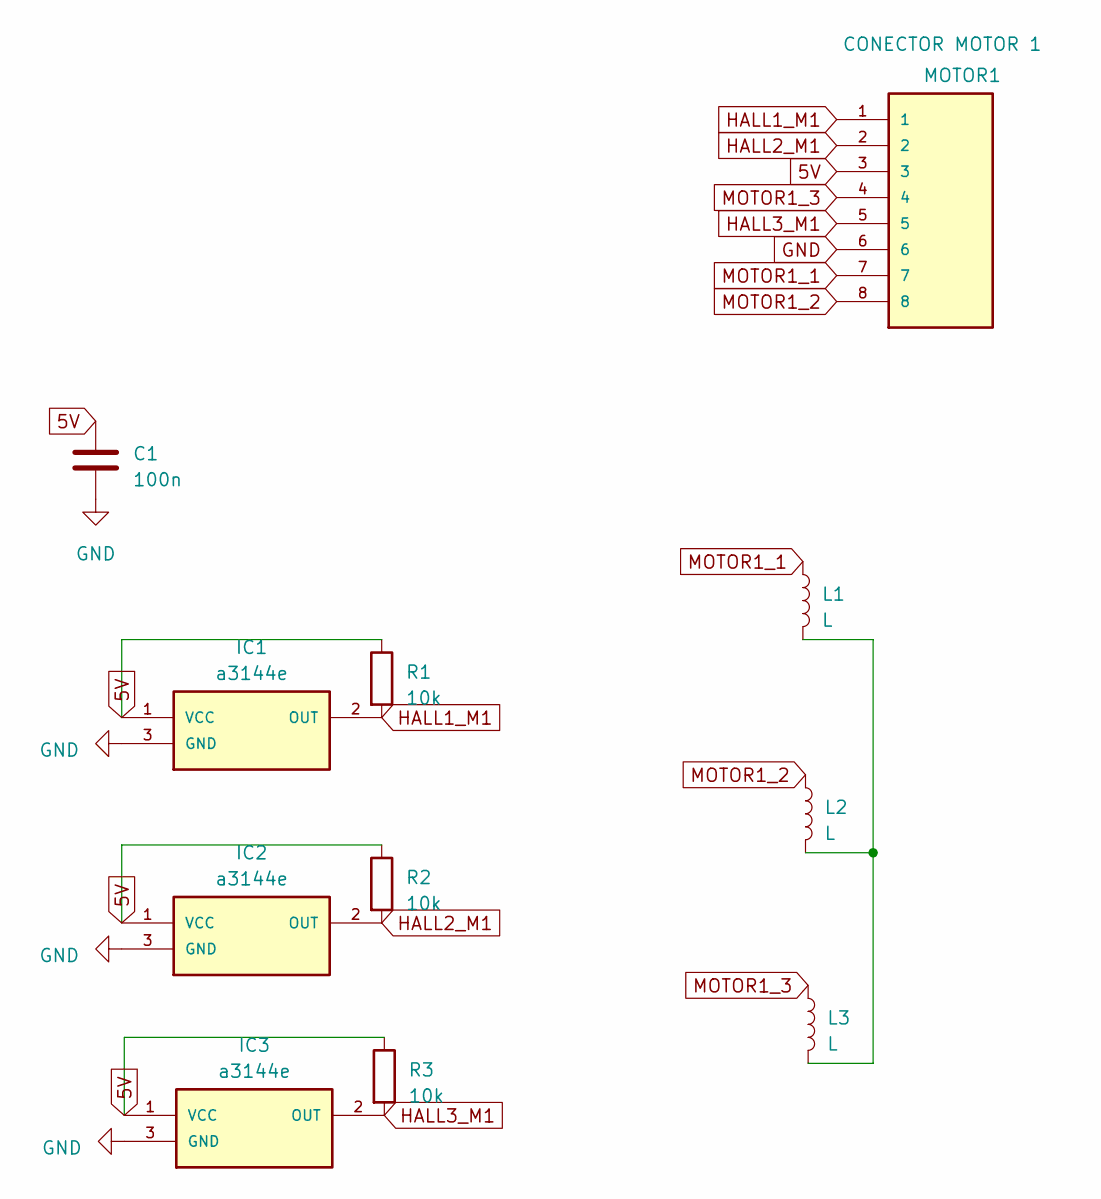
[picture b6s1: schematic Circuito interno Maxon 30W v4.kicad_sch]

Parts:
C1: 100n; C_0805_2012Metric
IC1, IC2, IC3: a3144e; SOT-23; MOUSER_PART_NUMBER 621-AH49ENTR-G1
L1, L2, L3: L; L_Axial_L11.0mm_D4.5mm_P15.24mm_Horizontal_Fastron_MECC
MOTOR1: CONECTOR MOTOR 1; TE_1586037-8b
R1, R2, R3: 10k; R_0805_2012Metric

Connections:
5V: C1.1, IC1.1 (VCC), IC2.1 (VCC), IC3.1 (VCC), MOTOR1.3, R1.1, R2.1, R3.1
GND: C1.2, IC1.3 (GND), IC2.3 (GND), IC3.3 (GND), MOTOR1.6
HALL1_M1: IC1.2 (OUT), MOTOR1.1, R1.2
HALL2_M1: IC2.2 (OUT), MOTOR1.2, R2.2
HALL3_M1: IC3.2 (OUT), MOTOR1.5, R3.2
MOTOR1_1: L1.1, MOTOR1.7
MOTOR1_2: L2.1, MOTOR1.8
MOTOR1_3: L3.1, MOTOR1.4
unnamed: L1.2, L2.2, L3.2
